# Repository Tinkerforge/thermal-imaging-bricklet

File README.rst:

Thermal Imaging Bricklet
========================

This repository contains the firmware source code and the hardware design
files. The documentation generator configs can be found at
https://github.com/Tinkerforge/generators

Repository Content
------------------

software/:
 * examples/: Examples for all supported languages
 * build/: Compiled files
 * src/: Source code of firmware
 * Makefile: Makefile to build project

hardware/:
 * Contains KiCad project files and additionally schematics as PDF

datasheets/:
 * Contains datasheets for sensors and complex ICs that are used

Hardware
--------

The hardware is designed with the open source EDA Suite KiCad
(http://www.kicad.org). Before you are able to open the files,
you have to install the Tinkerforge kicad-libraries
(https://github.com/Tinkerforge/kicad-libraries). You can either clone
them directly in hardware/ or clone them in a separate folder and
symlink them into hardware/
(ln -s kicad_path/kicad-libraries project_path/hardware). After that you
can open the .pro file in hardware/ with KiCad and from there view and
modify the schematics and the PCB layout.

Software
--------

If you want to do your own Brick/Bricklet firmware development we highly
recommend that you use our build environment setup script and read the
tutorial (https://www.tinkerforge.com/en/doc/Tutorials/Tutorial_Build_Environment/Tutorial.html).

To compile the C code we recommend you to install the newest GNU Arm Embedded
Toolchain (https://launchpad.net/gcc-arm-embedded/+download).
You also need to install bricklib2 (https://github.com/Tinkerforge/bricklib2).

You can either clone it directly in software/src/ or clone it in a
separate folder and symlink it into software/src/
(ln -s bricklib_path/bricklib2 project_path/software/src/). Finally make sure to
have CMake installed (http://www.cmake.org/cmake/resources/software.html).

After that you can build the firmware by invoking make in software/.
The firmware (.zbin) can then be found in software/build/ and uploaded
with brickv (click button "Flashing" on start screen).

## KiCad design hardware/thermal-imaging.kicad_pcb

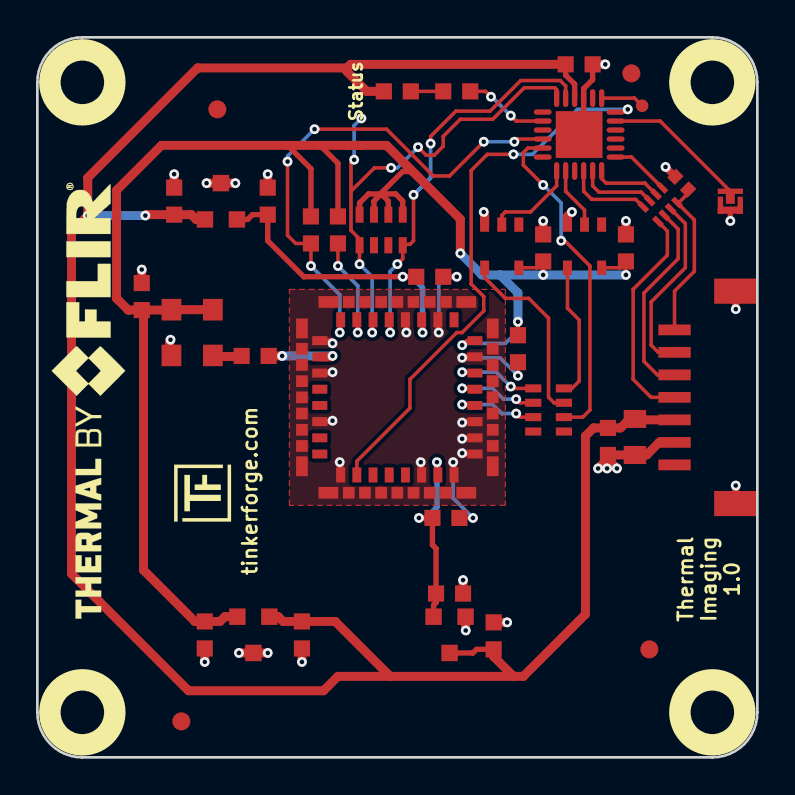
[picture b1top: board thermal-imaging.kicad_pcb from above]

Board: 2 copper layers, 40.0 x 40.0 mm, 44 parts (1 on the bottom side), 32 nets.

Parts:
C1: 10uF; C0805
C2, C9, C10, C11, C13, C14, C15: 1uF; C0603F
C3, C4, C5, C6, C7, C8, C12: 100nF; C0603F
C16: 220pF; C0402F
D1: LED blue; D0603F
Fiducial_Mark: VAL**; Fiducial_Mark
Fiducial_Mark#2, Fiducial_Mark#3, Fiducial_Mark#4: VAL**; Fiducial_Mark
P1: CON-SENSOR; CON-SENSOR2
P2: Boot; SolderJumper
P3: Debug; DEBUG_PAD
Q1: 25MHz; CRYSTAL_5032
R1, R2, R3: 1k; R0603F
R4: 100; R0603F
RP1: 82; 4X0402
RP2: 1k; 0603X4
RP3: 220; 0603X4
U1: XMC1302-32; QFN24-4x4mm-0.5mm
U2, U3: 74LVC1G17; SOT23-5
U4: FLIR-Lepton; Lepton_105028
U5, U6: AP7333-28SAG; SOT23-3
U7: MCP1700T-1202E/TT; SOT23-3R
U8, U9, U10, U11: DRILL; DRILL_NP
VAL: CE_5mm

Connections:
3V3: C1.2, C2.2, C3.2, C9.2, C10.2, C11.2, D1.1, P1.3, U1.10, U5.1, U6.1, U7.1
+1.2V_INT: C6.2, C15.2, U4.7, U7.2
+2.8V: C4.1, C5.1, C7.1, C12.1, C13.2, Q1.1, Q1.4, R2.2, R3.2, RP2.1, RP2.2, RP2.3, RP2.4, U2.5, U3.5, U4.16, U5.2
+2.8V_INT: C8.1, C14.2, U4.19, U6.2
GND: C1.1, C2.1, C3.1, C4.2, C5.2, C6.1, C7.2, C8.2, C9.1, C10.1, C11.1, C12.2, C13.1, C14.1, C15.1, C16.1, P1.2, P1.EP, P2.1, Q1.2, U1.9, U1.EXP, U2.3, U3.3, U4.1, U4.6, U4.8, U4.9, U4.10, U4.11, U4.15, U4.18, U4.20, U4.25, U4.27, U4.30, U4.SHD, U5.3, U6.3, U7.3
M-CLK: U1.19, U2.2
M-CS: U1.20, U3.2
M-MISO: RP3.6, U1.17
unnamed: C16.2, P1.7, RP1.8
unnamed: D1.2, R1.2
unnamed: P1.4, RP1.5
unnamed: P1.5, RP1.6
unnamed: P1.6, RP1.7
unnamed: P2.2, U1.5
unnamed: P3.1, U1.7
unnamed: Q1.3, R4.1
unnamed: R1.1, U1.14
unnamed: R2.1, U4.23
unnamed: R4.2, U4.26
unnamed: RP3.1, U4.14
unnamed: RP3.2, U4.13
unnamed: RP3.3, U4.12
unnamed: RP3.7, U2.4
unnamed: RP3.8, U3.4
RESET: R3.1, U1.16, U4.24
S-CLK: RP1.3, U1.23
S-CS: RP1.4, U1.22
S-MISO: RP1.1, U1.1
S-MOSI: RP1.2, U1.24
SCL: RP2.8, U1.11, U4.21
SDA: RP2.5, U1.12, U4.22
VSYNC: U1.6, U4.2

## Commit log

2017-02-07 inital checkin
2017-02-07 Add datasheets
2017-02-07 adding datasheets
2017-02-07 basic schematic, first placement
2017-02-08 routing completed
2017-02-08 add description text
2017-02-24 fix wrong footprint
2017-03-10 Add initial stub implementation (defines and initialization)
2017-03-14 change pin error note
2017-03-20 Ad crc16.c to makefile
2017-03-20 Use P2_10 for debug, enable crc
2017-03-20 Define baudrates properly
2017-03-20 Fix typo
2017-03-20 Add initial packet handling
    This is still WIP, currently it is too slow to read a packet and transfer it through SPI at the same time.
2017-03-20 Use memcpy instead of for-loop
2017-03-20 For now we send the image after we read one completely
2017-03-20 Call callback handler directly
2017-03-20 Use 8MHz SPI clock speed
2017-03-20 Do receive completely in interrupt for 16 bytes at a time
2017-03-20 Call callback after we received all 15 bytes
2017-03-20 increment by row instead of line
2017-03-20 Check if we received packet before
2017-03-20 We now try to receive one image completely before we send it.
2017-03-21 add vsync pin change hint
2017-03-22 Remove unused communication callback
2017-03-22 Add XMC eru functions
2017-03-22 Implement grey scale and temperature callbacks
2017-03-22 Update priorities, pins etc
2017-03-22 Add vsync ISR and implement proper reception of 27 frames per second
2017-03-22 Remove unused code
2017-03-23 fix text orientation
2017-03-24 Change name from Temperature to Raw and Grey Scale to Image
2017-03-24 Change direction of packet transfer
2017-03-24 Add proper handling for callback enable bitmask
2017-03-24 Add gain control config functions
2017-03-24 Disable SPI/I2C properly if the other one is enabled
2017-03-24 Use constants
2017-03-24 Return from interrupt if interface is not SPI
2017-03-24 Add missing header
2017-03-24 Enable config handler after frame is done
2017-03-24 Fix row/col names
2017-03-24 Add defines and enums
2017-03-30 Test for packet 0 instead of discard packet
2017-03-30 Make sure fifo is empty before we start irqs
2017-03-30 Add initialization values
2017-03-30 Add crc check function (currently unused)
2017-03-30 Enable agc, disable tlinear by default on init
2017-03-30 Set sync to false at start of sync and don't deselect CS after sync
2017-03-30 Update configuration names
2017-03-30 Add missing id and crc to telemetry
2017-03-30 Update names
2017-03-31 Put irq handler in ram
2017-03-31 Add support for getter
2017-03-31 Only stream image if crc is OK
2017-03-31 Add ongoing manual stream boolean
2017-03-31 Put temperature and status information in same sequence
2017-04-03 Don't use sync signal if transfer is currently still active
2017-04-03 Use large input hysteresis
2017-04-03 Remove debug
2017-04-03 Make sure SPI select pin is high if SPI is not used
2017-04-03 deselect SPI after sync
2017-04-06 change text orientation
2017-04-06 Change direction around, so that by default the Bricklets works as a normal camera, not as a selfie camera
2017-04-12 Add rx/tx information to allow for hald-fuplex bootstrapper flashing
2017-05-08 fix vsync connection, footprints
2017-05-12 fix part texts
2017-05-12 Fix CE logo
2017-06-02 specify oscillator frequency
2017-08-11 specify filter circuit
2017-08-28 add flir logo
2017-09-19 specify processor type
2017-11-06 Add 3d information (tbc)
2017-11-06 Add final schematic
2017-11-07 Fix rx/tx mixup
2017-11-07 Split status into ffc status and temperature warnings
2017-11-08 Fix temperature warning bug
2017-11-20 Add 3d information (final)
2017-11-20 Add 3d model (*.step & *.FCStd)
2017-11-20 Fix path to 3d model of FLIR module
2017-11-23 Add Python examples
2017-11-23 Add C# examples
2017-11-23 Fix typos
2017-11-24 Add Java examples
2017-11-24 java: Add missing serialVersionUID
2017-11-28 Update examples from generator
2017-11-29 Add C example
2017-11-30 Adding MATLAB/Octave create image example
2017-12-04 Adding MATLAB live video example
2017-12-04 Fix typo in MATLAB create image example
2017-12-05 Finalize MATLAB/Octave examples
2017-12-07 mathematica: Also generate .nb files
2017-12-21 Add initial version of CES Flir demo
2017-12-21 Add working version
2017-12-21 Add humidity, air pressure and ambient light support
2017-12-21 Add Tinkerforge logo
2017-12-21 Final version but with performance problems
2017-12-22 Minor adjustments
2017-12-27 Add spotmeter measurements
2017-12-28 Adapt path for Raspberry Pi Demo
2017-12-28 Add autostart scripts
2017-12-28 Add /.config/autostart/ config file
2018-02-02 c: Update example
2018-02-19 javascript: Close div tag correctly
2018-02-20 Cleanup KiCad libraries config
    Ensure LibDir=kicad-libraries and LibName1=tinkerforge.
    Remove special library.
2018-02-21 Remove unused length check (length=0 can't happen)
2018-02-22 delphi: Use correct type for image parameter
2018-02-23 Remove incomplete marker from most callback examples
2018-04-25 Make sure that lepton always uses low gain mode if high range is configured (otherwise the high range can't be reached)
2018-04-25 Add git ref for 2.0.1
2018-05-24 perl: Use strict in examples
2018-06-18 Change capacitor footprint(s) to C0402F
2018-06-28 Fix readme
2018-07-11 Add Makefile with docker support
2018-07-11 Remove obsolete generate_makefile scripts
2018-07-11 Update directory structure and build instructions
2018-10-04 Increase version for new release (changes in bricklib2)
2018-10-04 Add rev to changelog
2018-11-06 Adapt struct names to common naming convention
2018-11-06 Add rust examples
2018-11-07 rust: Accept host names for ip connection, fix naming inconsistencies
2018-11-07 rust: Rename callback receivers.
2018-12-14 Add go examples.
2018-12-18 go: Change import path.
2018-12-18 go: Change import path again.
2018-12-20 rust: Reformat examples.
2019-01-24 mqtt: Add examples.
2019-01-24 mqtt: Remove executable bit in example permissions.
2019-01-24 go: Minor example fixes.
2019-01-25 Fix comment in callback examples.
2019-03-25 go: Fix comment typo.
2019-05-28 Add support for logging (turned off by default)
2019-05-28 Move CRC check outside of sync interrupt
    The CRC check sometimes took so long that the SPITFP irq
    would start to transfer zeros and introduce CRC errors in the
    SPI protocol
2019-05-28 Improve SPI IRQ performance
    Use local pointer to save the time for accessing the struct
2019-07-01 Add Thermal Image -> LCD 128x64 example
2019-08-13 Double buffer lepton statistics to prevent statistics tearing
2019-08-13 spaces -> tabs
2019-08-13 Changelog entry for 2.0.4
2019-08-22 c: Adapt to bindings changes
2019-09-19 Fix vertical orientation of images transfered by getter.
2020-01-13 example_live_video: Add maximized mode. Fix python2 and window close.
2020-01-14 examples: Use python3 input by default.
2020-02-05 Don't start new frame read if a manual transfer is ongoing
2020-02-05 Add Set/GetLinearFluxParameters API
2020-02-05 Fix accidential c+p error
2020-02-05 Add ref for 2.0.5
2020-02-26 examples: Update "Change UID" comment style
2020-03-18 Whitespace
2020-03-18 rust: Update to new skeleton
2020-06-29 Fix typo in changelog
2020-06-29 Fix another typo in changelog
2020-08-19 Add uc examples.
2020-08-25 uc: Adapt example to new skeleton
2020-08-27 uc: Fix warnings.
2020-08-31 uc: Use fixed-with placeholders in format strings.
2020-09-02 uc: Add example driver note.
2020-09-28 Add palette source comment to examples.
2021-06-24 python: Add OpenCV exampels
2021-10-25 Update KiCad link
    https://www.kicad.org/blog/2021/10/Avoid-links-to-former-kicad-domain/
2022-04-19 examples: uc: Rename TF_HalContext to TF_HAL.
2022-04-26 uc: Adapt to bindings changes
2022-07-06 Add license files.
2023-03-10 Add FFC shutter mode and normalization API
2024-03-14 Add ref for 2.0.6

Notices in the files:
hardware/thermal-imaging.kicad_pcb:
Licensed under CERN OHL v.1.1
Copyright (©) 2017, B.Nordmeyer
Copyright Tinkerforge GmbH 2017.
This documentation describes Open Hardware and is licensed under the
CERN OHL v. 1.1.
